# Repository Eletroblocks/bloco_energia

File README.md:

# energia
Fornece ENERGIA ELÉTRICA para os blocos seguintes.

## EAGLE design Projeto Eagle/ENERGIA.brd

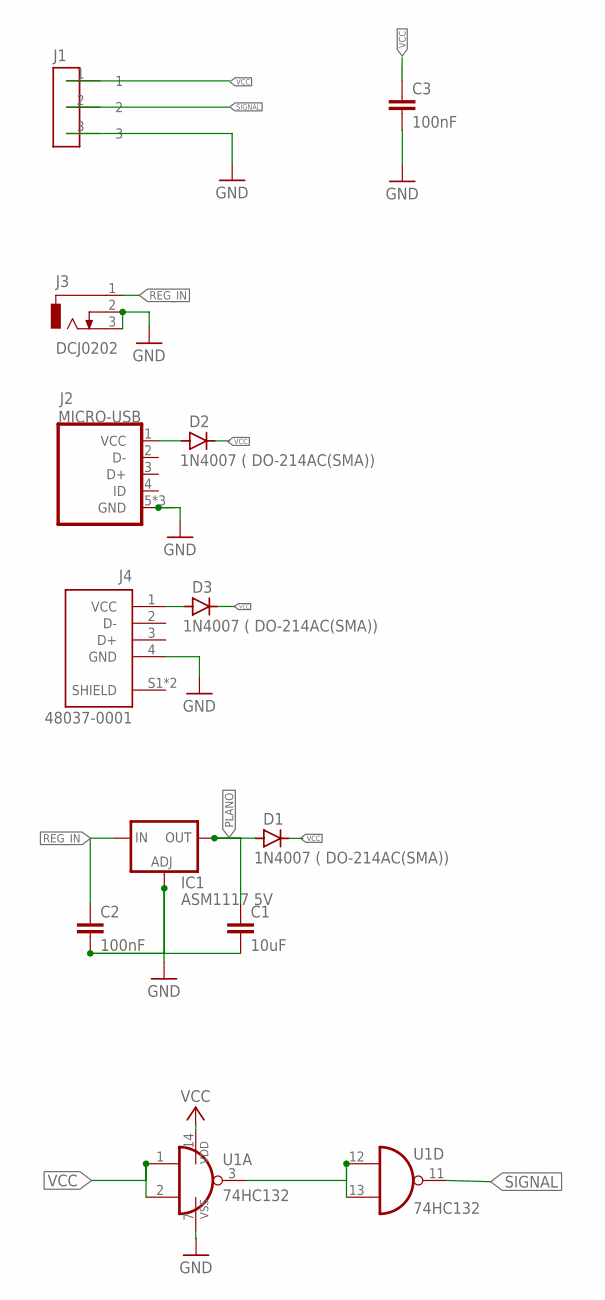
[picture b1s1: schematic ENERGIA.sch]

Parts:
C1: 10uF; C0805
C2, C3: 100nF; C0805
D1, D2, D3: 1N4007 ( DO-214AC(SMA)); SMA-DO214AC
IC1: ASM1117 5V; SOT223
J1: CONECTOR; 3CONECTOR
J2: MICRO-USB
J3: DCJ0202
J4: 48037-0001; MOLEX_48037-0001
U1: 74HC132; SO14

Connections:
GND: C1.2, C2.2, C3.2, IC1.1 (ADJ), J1.3, J2.5 (GND), J2.GND1 (GND), J2.GND2 (GND), J3.2, J3.3, J4.4 (GND), U1.7 (VSS)
unnamed: D2.A, J2.1 (VCC)
unnamed: U1.3 (O), U1.12 (I0), U1.13 (I1)
unnamed: D3.A, J4.1 (VCC)
PLANO: C1.1, D1.A, IC1.4 (OUT)
REG_IN: C2.1, IC1.3 (IN), J3.1
SIGNAL: J1.2, U1.11 (O)
VCC: C3.1, D1.K (C), D2.K (C), D3.K (C), J1.1, U1.1 (I0), U1.2 (I1), U1.14 (VDD)

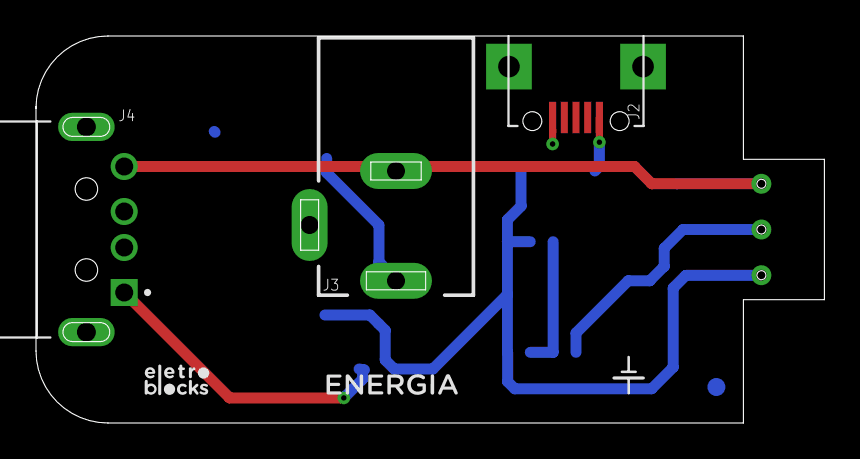
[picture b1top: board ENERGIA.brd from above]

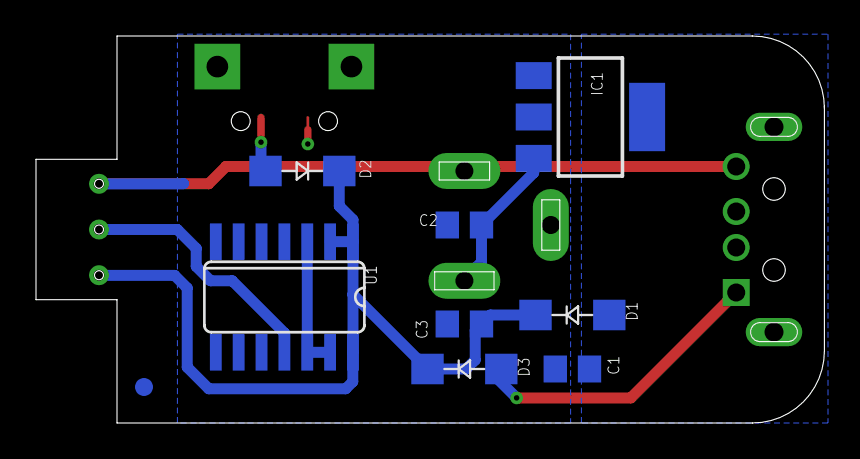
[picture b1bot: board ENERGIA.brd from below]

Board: 2 copper layers, 43.8 x 21.5 mm, 13 parts (9 on the bottom side), 8 nets.

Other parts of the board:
U$1: FIDUCIAL_G10

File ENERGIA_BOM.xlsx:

BOM LIST ENERGIA
DESCRIPTION | QUANTITY | POSITION | PART NUMBER
CAPACITOR 100nF/50V 0805 | 3 | C1,C2,C3 | UMF212B7104KGHT, can be replaced to similar
SCHOTTKY DIODE | 3 | D1,D2,D3 | 1N5819HW-7-F
5V VOLTAGE REGULATOR AMS1117 5V SOT-223 | 1 | IC1 | ASM1117
NAND SHCMITT TRIGGER | 1 | U1 | 74HC132D,653
MICRO-USB FEMALE | 1 | J2 | 1050170001
JACK | 1 | J3 | PJ-102A
USB MALE | 1 | J4 | 48037-0001
FEMALE CONNECTOR | 1 | J1 | THIS COMPONENT IS PROVIDE BY ELETROBLOCKS

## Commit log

2020-11-23 init project
2020-11-23 adição de nova entrada USB
2020-11-23 adição de label para versionamento, correção de posição de vias e adição de plano GND no TOP layer
2020-12-28 organizando arquivos
2020-12-28 imagem

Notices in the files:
parts and their libraries:
dicons: Copyright (C) 2004, Bob Starr (rtzaudio@mindspring.com)
